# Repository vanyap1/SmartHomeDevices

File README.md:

# SmartHomeDevices
Smart Home consolidated devices project

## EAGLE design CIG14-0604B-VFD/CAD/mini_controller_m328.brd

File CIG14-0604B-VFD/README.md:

# CIG14-0604B-VFD
CIG14-0604B display controller 
Проект створено в Microchip studio.
Плата контролера - Eagle.

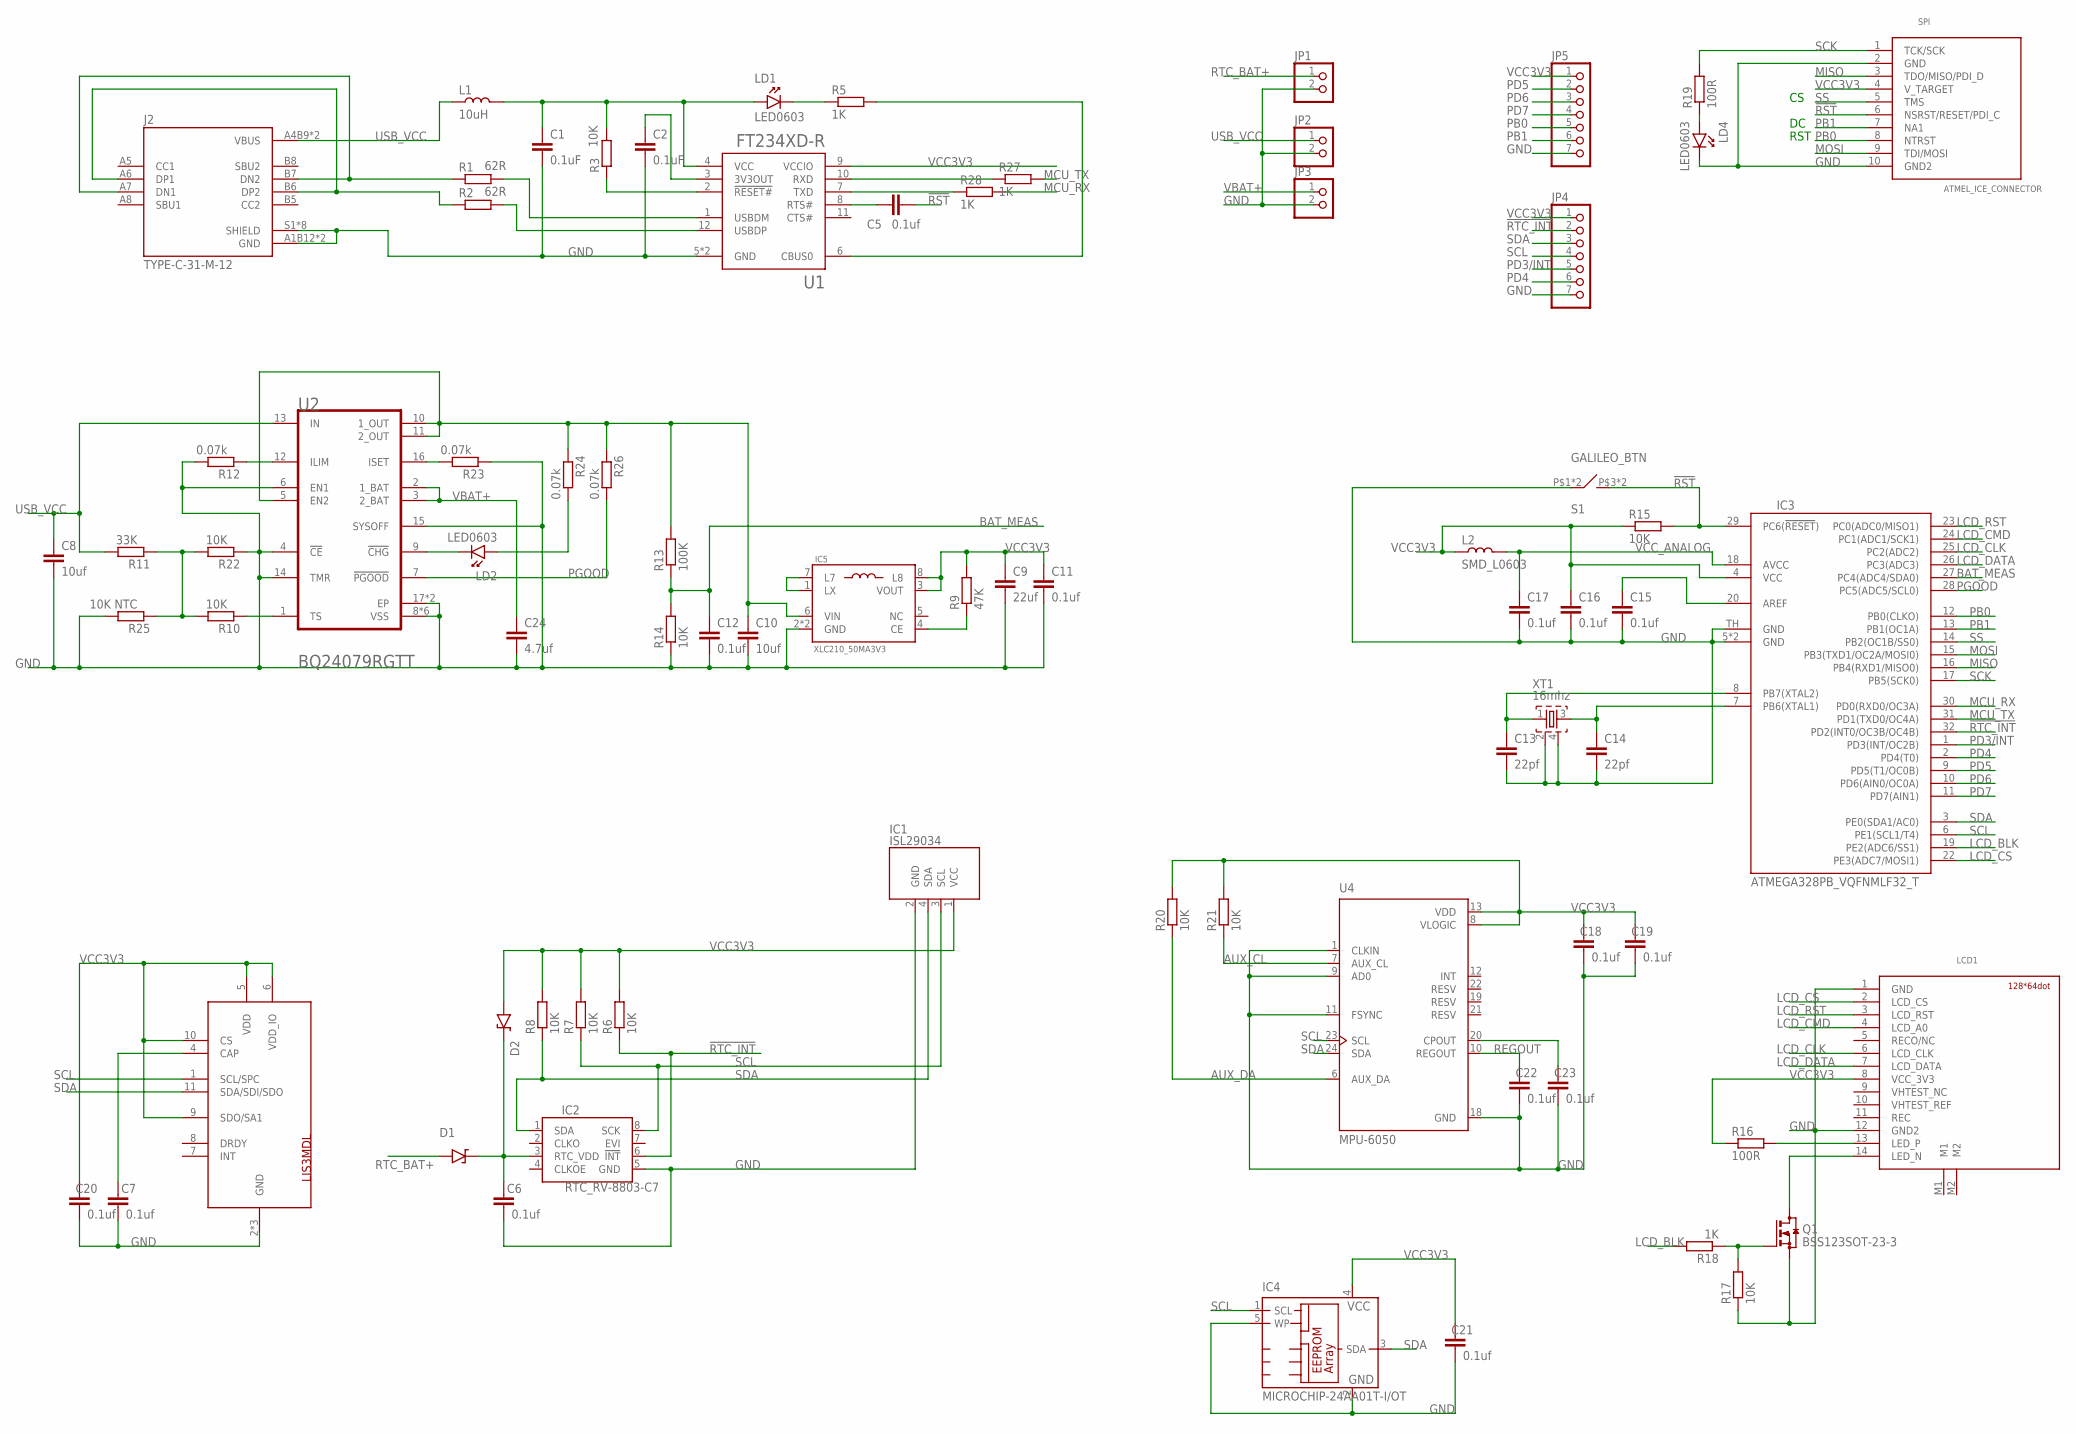
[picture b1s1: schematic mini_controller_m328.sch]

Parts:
C1, C2: 0.1uF; 0603
C5, C6, C7, C11, C12, C15, C16, C17, C18, C19, C20, C21, C22, C23: 0.1uf; 0603
C8: 10uf; 1206
C9: 22uf; 0805
C10: 10uf; 0603
C13, C14: 22pf; 0603
C24: 4.7uf; 0805
D1, D2: D_SOD323; SOD-323_D
IC1: ISL29034
IC2: RTC_RV-8803-C7; C7_RTC
IC3: ATMEGA328PB_VQFNMLF32_T; MLF32-TH
IC4: MICROCHIP-24AA01T-I/OT; SOT-23(5)
IC5: XLC210_50MA3V3; XCL210_50MA3V3
J2: TYPE-C-31-M-12; HRO_TYPE-C-31-M-12
JP1, JP2, JP3: PINHD-1X2; 1X02
JP4, JP5: PINHD-1X7; 1X07
L1: 10uH; 0603
L2: SMD_L0603; 0603
LCD1: ALE_LCD_128X64; ALE_LCD_14PIN_CONNECTOR
LD1, LD2, LD4: LED0603; 0603_P
Q1: BSS123SOT-23-3; SOT-23(3)
R1, R2: 62R; 0603
R3, R6, R7, R8, R10, R14, R15, R17, R20, R21, R22: 10K; 0603
R5, R18, R27, R28: 1K; 0603
R9: 47K; 0603
R11: 33K; 0603
R12, R23, R24, R26: 0.07k; 0603
R13: 100K; 0603
R16, R19: 100R; 0603
R25: 10K NTC; 0603
S1: GALILEO_BTN; GALILEO_VERT_BTN
SPI: ATMEL_ICE_CONNECTOR; MINI10P_SPI/JTAG/PDI
U1: FT234XD-R; IC_FT234XD-R
U2: TEXAS_INSTRUMENTS_BQ24079RGTTTEXAS_INSTRUMENTS_BQ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; TEXAS_INSTRUMENTS_BQ24079RGTT_0
U4: MPU-6050; QFN50P400X400X95-24N
U$1: LIS3MDL; LGA-12
XT1: 16mhz; QUARTZ_3X3MM

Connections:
!RST: C5.2, IC3.29 (PC6(!RESET!)), R15.2, S1.P$3 (4), S1.P$4 (4), SPI.6 (NSRST/RESET/PDI_C)
!RTC_INT: IC2.6 (!INT), IC3.32 (PD2(INT0/OC3B/OC4B)), JP4.2, R6.1
AUX_CL: R21.1, U4.7 (AUX_CL)
AUX_DA: R20.1, U4.6 (AUX_DA)
BAT_MEAS: C12.1, IC3.27 (PC4(ADC4/SDA0)), R13.1, R14.2
DM2: R1.2, U1.1 (USBDM)
DP2: R2.2, U1.12 (USBDP)
GND: C1.2, C2.2, C6.2, C7.2, C8.2, C9.2, C10.2, C11.2, C12.2, C13.2, C14.2, C15.2, C16.2, C17.2, C18.2, C19.2, C20.2, C21.2, C22.2, C23.2, C24.2, IC1.2 (GND), IC2.5 (GND), IC3.5 (GND), IC3.21 (GND), IC3.TH (GND), IC4.2 (GND), IC4.5 (WP), IC5.2 (GND), IC5.9 (GND), J2.A1B12 (GND), J2.B1A12 (GND), J2.S1 (SHIELD), J2.S2 (SHIELD), J2.S3 (SHIELD), J2.S4 (SHIELD), J2.S5 (SHIELD), J2.S6 (SHIELD), J2.S7 (SHIELD), J2.S8 (SHIELD), JP1.2, JP2.2, JP3.2, JP4.7, JP5.7, LCD1.1 (GND), LCD1.12 (GND2), LD4.1 (K), Q1.2 (S), R12.2, R14.1, R17.1, R22.1, R23.1, R25.2, S1.P$1 (1), S1.P$2 (1), SPI.2 (GND), SPI.10 (GND2), U1.5 (GND), U1.13 (GND), U2.4 (!CE!), U2.6 (EN1), U2.8 (VSS), U2.14 (TMR), U2.15 (SYSOFF), U2.17 (EP), U2.17-2 (EP), U2.PAD_1 (VSS), U2.PAD_2 (VSS), U2.PAD_3 (VSS), U2.PAD_4 (VSS), U2.PAD_5 (VSS), U4.1 (CLKIN), U4.9 (AD0), U4.11 (FSYNC), U4.18 (GND), U$1.2 (GND), U$1.3 (GND), U$1.12 (GND), XT1.2, XT1.4
LCD_BLK: IC3.19 (PE2(ADC6/SS1)), R18.2
LCD_CLK: IC3.25 (PC2(ADC2)), LCD1.6 (LCD_CLK)
LCD_CMD: IC3.24 (PC1(ADC1/SCK1)), LCD1.4 (LCD_A0)
LCD_CS: IC3.22 (PE3(ADC7/MOSI1)), LCD1.2 (LCD_CS)
LCD_DATA: IC3.26 (PC3(ADC3)), LCD1.7 (LCD_DATA)
LCD_RST: IC3.23 (PC0(ADC0/MISO1)), LCD1.3 (LCD_RST)
MCU_RX: IC3.30 (PD0(RXD0/OC3A)), R28.2
MCU_TX: IC3.31 (PD1(TXD0/OC4A)), R27.2
MISO: IC3.16 (PB4(RXD1/MISO0)), SPI.3 (TDO/MISO/PDI_D)
MOSI: IC3.15 (PB3(TXD1/OC2A/MOSI0)), SPI.9 (TDI/MOSI)
unnamed: LCD1.13 (LED_P), R16.2
unnamed: LCD1.14 (LED_N), Q1.3 (D)
unnamed: IC5.1 (LX), IC5.7 (L7)
unnamed: Q1.1 (G), R17.2, R18.1
unnamed: IC5.4 (CE), R9.1
unnamed: R10.2, R11.1, R22.2, R25.1
unnamed: C1.1, L1.2, LD1.2 (A), R3.2, U1.4 (VCC)
unnamed: C13.1, IC3.8 (PB7(XTAL2)), XT1.1
unnamed: C2.1, U1.3 (3V3OUT)
unnamed: LD1.1 (K), R5.1
unnamed: R5.2, U1.6 (CBUS0)
unnamed: C14.1, IC3.7 (PB6(XTAL1)), XT1.3
unnamed: LD2.1 (K), U2.9 (!CHG!)
unnamed: R27.1, U1.10 (RXD)
unnamed: C5.1, U1.8 (RTS#)
unnamed: LD4.2 (A), R19.1
unnamed: C23.1, U4.20 (CPOUT)
unnamed: R10.1, U2.1 (TS)
unnamed: C6.1, D1.K, D2.K, IC2.3 (RTC_VDD)
unnamed: C15.1, IC3.20 (AREF)
unnamed: J2.A7 (DN1), J2.B7 (DN2), R1.1
unnamed: J2.A6 (DP1), J2.B6 (DP2), R2.1
unnamed: R12.1, U2.12 (ILIM)
unnamed: C10.1, IC5.6 (VIN), R13.2, R24.1, R26.1, U2.5 (EN2), U2.10 (1_OUT), U2.11 (2_OUT)
unnamed: LD2.2 (A), R24.2
unnamed: R23.2, U2.16 (ISET)
unnamed: R28.1, U1.7 (TXD)
unnamed: C7.1, U$1.4 (CAP)
PB0: IC3.12 (PB0(CLKO)), JP5.5, SPI.8 (NTRST)
PB1: IC3.13 (PB1(OC1A)), JP5.6, SPI.7 (NA1)
PD3/INT: IC3.1 (PD3(INT/OC2B)), JP4.5
PD4: IC3.2 (PD4(T0)), JP4.6
PD5: IC3.9 (PD5(T1/OC0B)), JP5.2
PD6: IC3.10 (PD6(AIN0/OC0A)), JP5.3
PD7: IC3.11 (PD7(AIN1)), JP5.4
PGOOD: IC3.28 (PC5(ADC5/SCL0)), R26.2, U2.7 (!PGOOD!)
REGOUT: C22.1, U4.10 (REGOUT)
RTC_BAT+: D1.A, JP1.1
SCK: IC3.17 (PB5(SCK0)), R19.2, SPI.1 (TCK/SCK)
SCL: IC1.3 (SCL), IC2.8 (SCK), IC3.6 (PE1(SCL1/T4)), IC4.1 (SCL), JP4.4, R7.1, U4.23 (SCL), U$1.1 (SCL/SPC)
SDA: IC1.4 (SDA), IC2.1 (SDA), IC3.3 (PE0(SDA1/AC0)), IC4.3 (SDA), JP4.3, R8.1, U4.24 (SDA), U$1.11 (SDA/SDI/SDO)
SER_RST: R3.1, U1.2 (!RESET#)
SS: IC3.14 (PB2(OC1B/SS0)), SPI.5 (TMS)
USB_VCC: C8.1, J2.A4B9 (VBUS), J2.B4A9 (VBUS), JP2.1, L1.1, R11.2, U2.13 (IN)
VBAT+: C24.1, JP3.1, U2.2 (1_BAT), U2.3 (2_BAT)
VCC3V3: C9.1, C11.1, C16.1, C18.1, C19.1, C20.1, C21.1, D2.A, IC1.1 (VCC), IC3.4 (VCC), IC4.4 (VCC), IC5.3 (VOUT), IC5.8 (L8), JP4.1, JP5.1, L2.1, LCD1.8 (VCC_3V3), R6.2, R7.2, R8.2, R9.2, R15.1, R16.1, R20.2, R21.2, SPI.4 (V_TARGET), U1.9 (VCCIO), U4.8 (VLOGIC), U4.13 (VDD), U$1.5 (VDD), U$1.6 (VDD_IO), U$1.9 (SDO/SA1), U$1.10 (CS)
VCC_ANALOG: C17.1, IC3.18 (AVCC), L2.2

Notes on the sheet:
RST

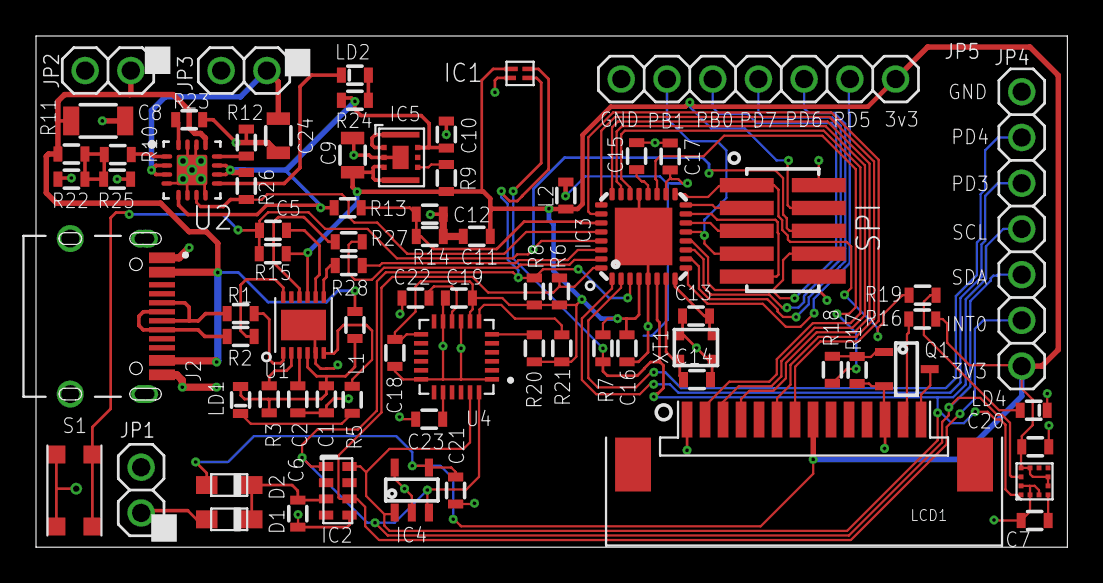
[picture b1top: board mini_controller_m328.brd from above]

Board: 2 copper layers, 57.3 x 28.4 mm, 76 parts (0 on the bottom side), 65 nets.

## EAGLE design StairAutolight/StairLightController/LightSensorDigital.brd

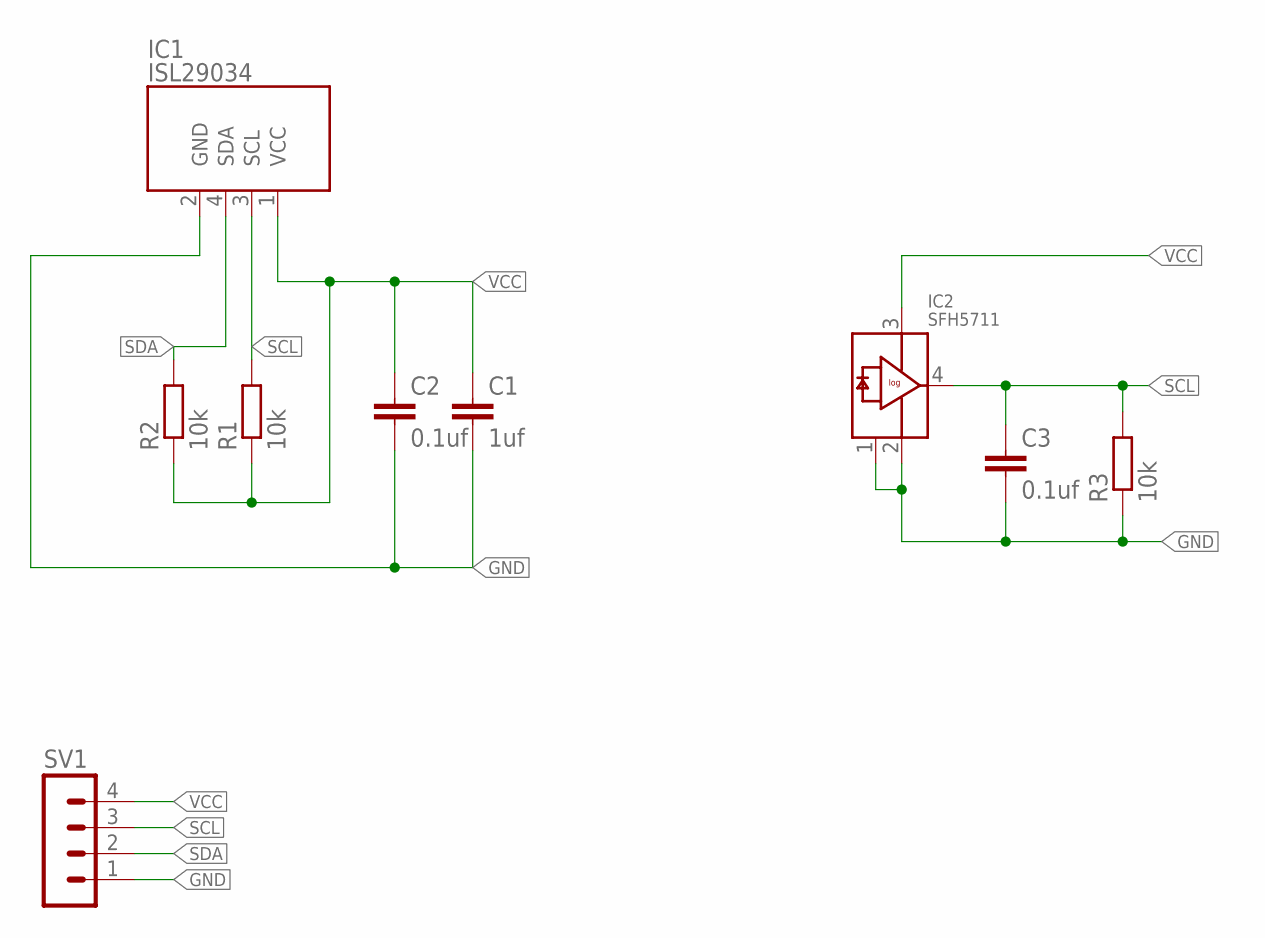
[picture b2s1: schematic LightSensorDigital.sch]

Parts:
C1: 1uf; 0603
C2, C3: 0.1uf; 0603
IC1: ISL29034
IC2: SFH5711
R1, R2, R3: 10k; 0603
SV1: MA04-1

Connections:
GND: C1.2, C2.2, C3.2, IC1.2 (GND), IC2.1, IC2.2, R3.1, SV1.1
SCL: C3.1, IC1.3 (SCL), IC2.4, R1.2, R3.2, SV1.3
SDA: IC1.4 (SDA), R2.2, SV1.2
VCC: C1.1, C2.1, IC1.1 (VCC), IC2.3, R1.1, R2.1, SV1.4

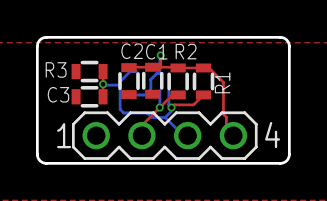
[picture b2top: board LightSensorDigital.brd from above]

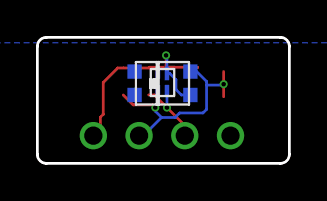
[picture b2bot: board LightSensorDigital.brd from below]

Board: 2 copper layers, 14.0 x 7.0 mm, 9 parts (2 on the bottom side), 4 nets.

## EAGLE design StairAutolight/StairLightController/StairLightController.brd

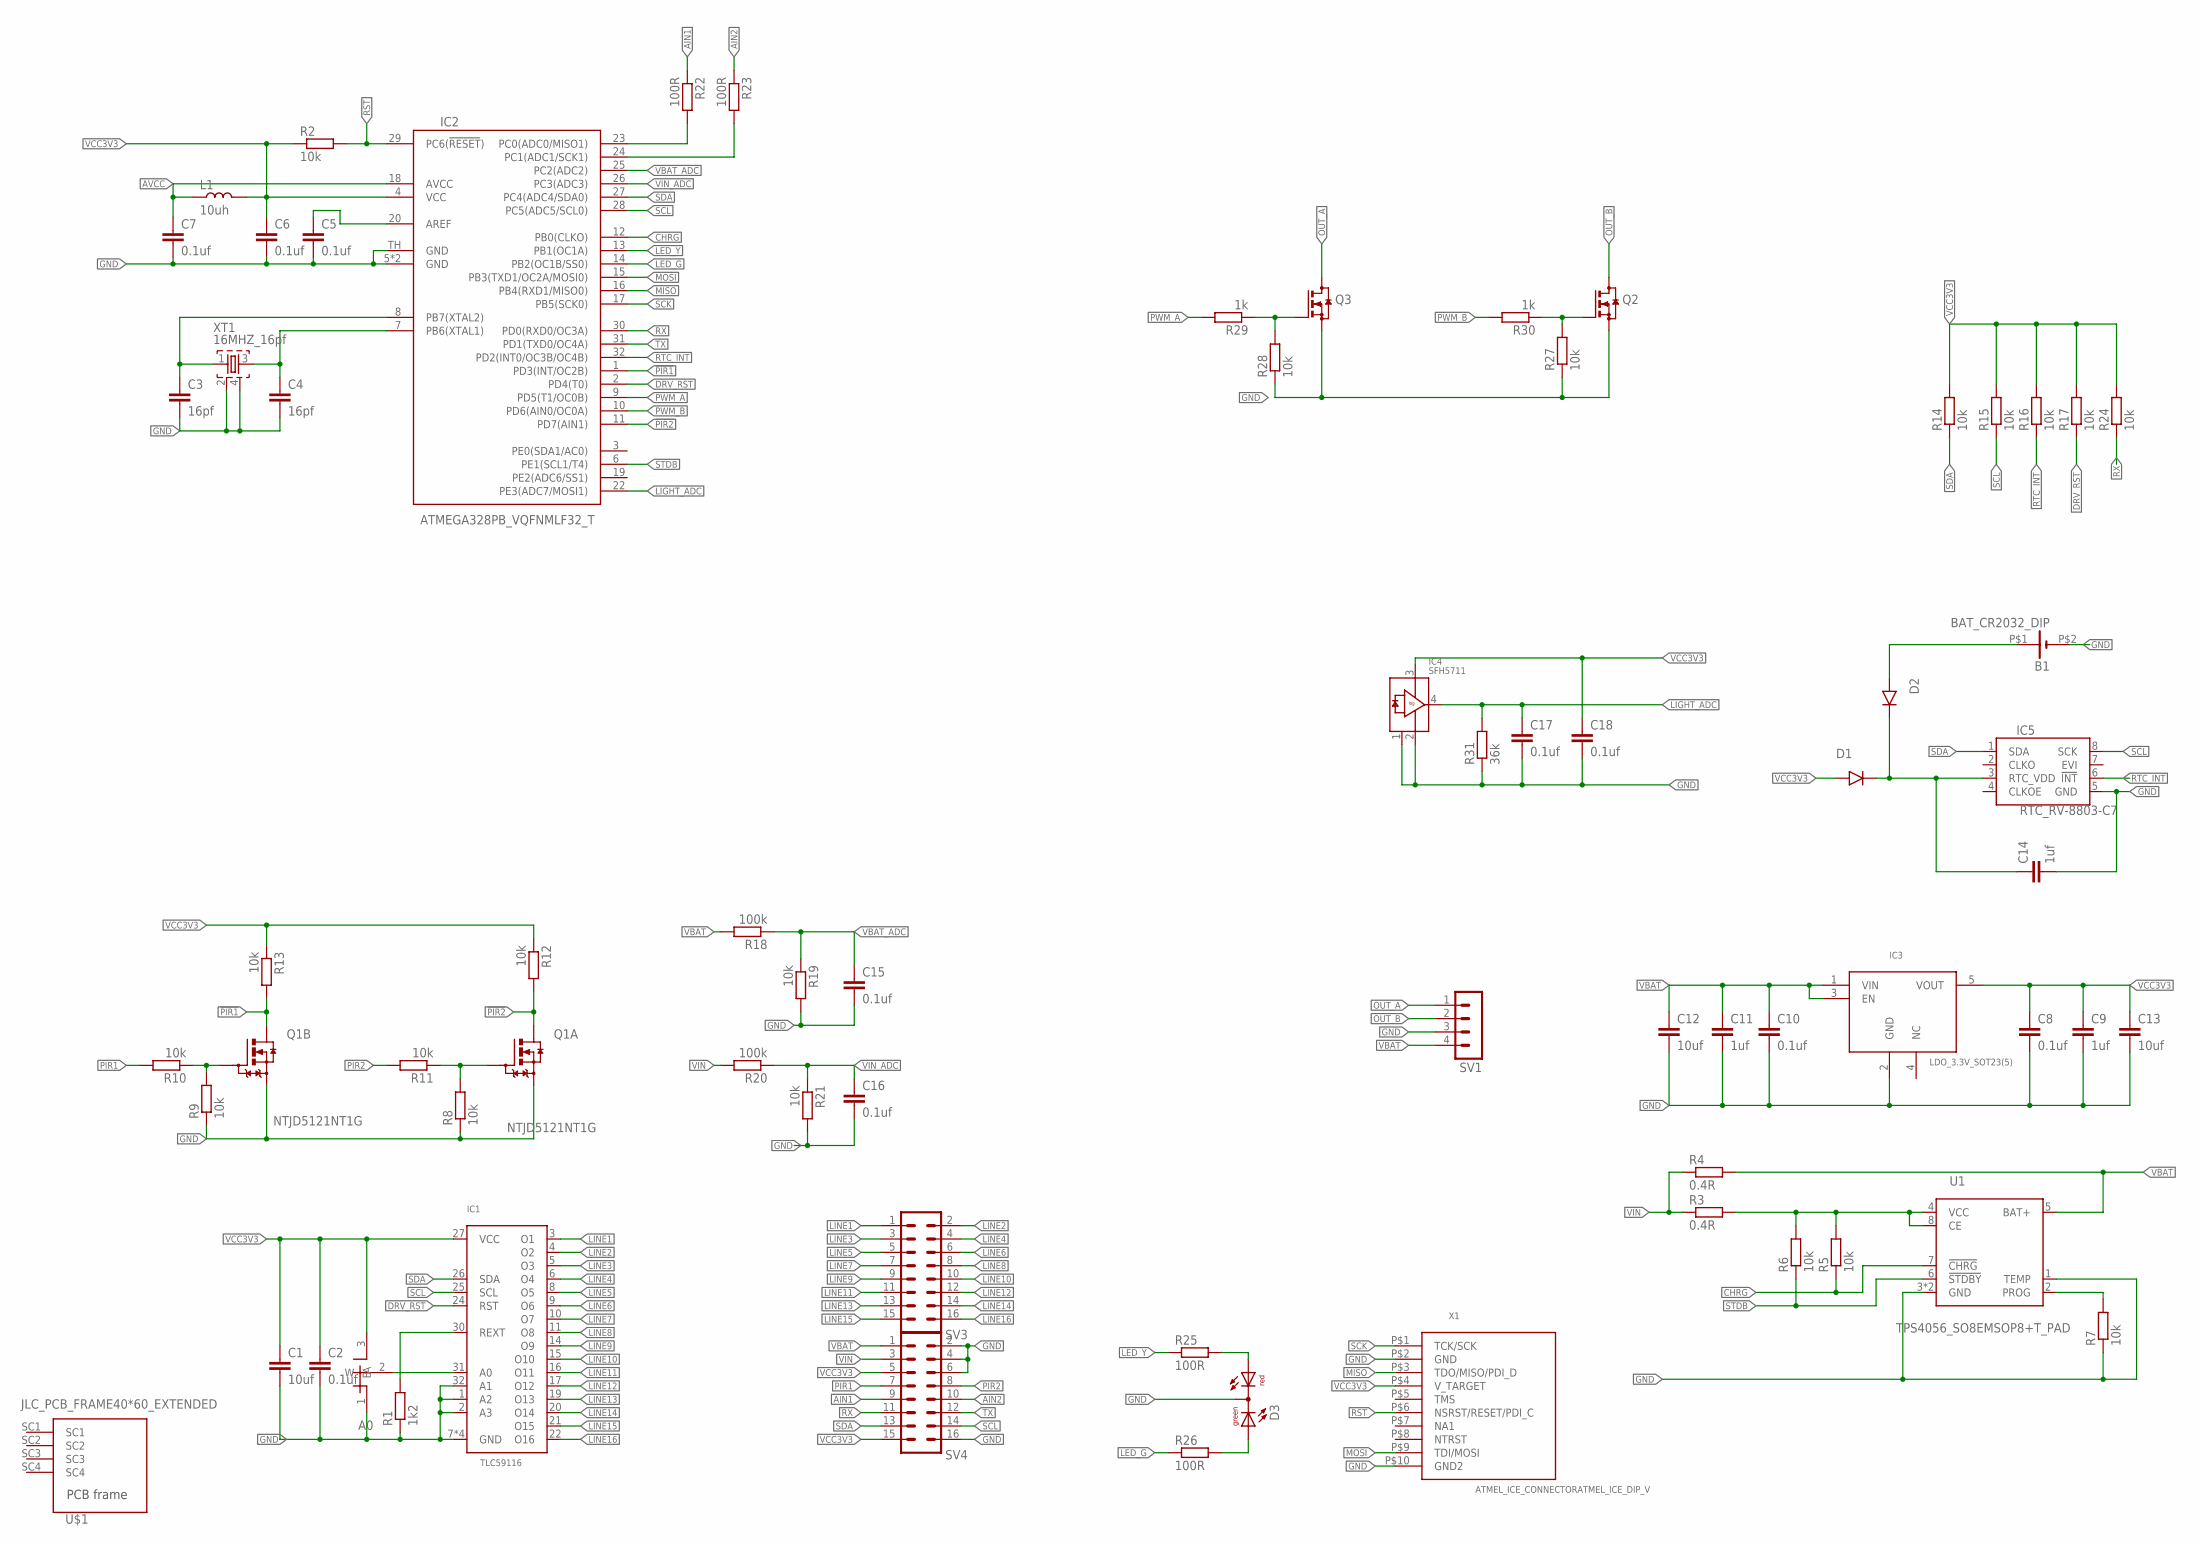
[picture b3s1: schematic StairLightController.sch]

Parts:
A0: SMD_SWITCH_JUMPER; 0603_JUMP
B1: BAT_CR2032_DIP; CR2032_DIP
C1: 10uf; 0603
C2, C5, C6, C7, C8, C10, C15, C16, C17, C18: 0.1uf; 0603
C3, C4: 16pf; 0603
C9, C11, C14: 1uf; 0603
C12, C13: 10uf; 1206
D1, D2: L1N4148WT1GSOD123_GALILE0_SMALL; SOD-123_MINI-SMA
D3: DUOLED5MM
IC1: TLC59116; MLF32-TH
IC2: ATMEGA328PB_VQFNMLF32_T; MLF32-TH
IC3: LDO_3.3V_SOT23(5); SOT-23(5)
IC4: SFH5711
IC5: RTC_RV-8803-C7; C7_RTC
L1: 10uh; 0603
Q1: NTJD5121NT1G; SOT363
Q2, Q3: BSS123SOT-23-3; SOT-23(3)
R1: 1k2; 0603
R2, R5, R6, R7, R8, R9, R10, R11, R12, R13, R14, R15, R16, R17, R19, R21, R24, R27, R28: 10k; 0603
R3, R4: 0.4R; 1206
R18, R20: 100k; 0603
R22, R23, R25, R26: 100R; 0603
R29, R30: 1k; 0603
R31: 36k; 0603
SV1: MA04-1
SV3, SV4: MA08-2
U1: TPS4056_SO8EMSOP8+T_PAD; EMSOP8+TPAD
U$1: JLC_PCB_FRAME40*60_EXTENDED; 40X60_SENSOR_UNIT_OPEN
X1: ATMEL_ICE_CONNECTORATMEL_ICE_DIP_V; MINI10P_SPI/JTAG/PDI_DIP_V
XT1: 16MHZ_16pf; QUARTZ_3X3MM

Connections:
!PIR1: IC2.1 (PD3(INT/OC2B)), Q1.3 (D), R13.2
!PIR2: IC2.11 (PD7(AIN1)), Q1.6 (D), R12.2
AIN1: R22.1, SV4.9
AIN2: R23.1, SV4.10
AVCC: C7.1, IC2.18 (AVCC), L1.1
CHRG: IC2.12 (PB0(CLKO)), R5.1, U1.7 (!CHRG)
DRV_RST: IC1.24 (RST), IC2.2 (PD4(T0)), R17.1
GND: A0.1 (A), B1.P$2 (-), C1.2, C2.2, C3.2, C4.2, C5.2, C6.2, C7.2, C8.2, C9.2, C10.2, C11.2, C12.2, C13.2, C14.2, C15.2, C16.2, C17.2, C18.2, D3.K (C), IC1.1 (A2), IC1.2 (A3), IC1.7 (GND), IC1.18 (GND), IC1.23 (GND), IC1.32 (A1), IC1.TH (GND), IC2.5 (GND), IC2.21 (GND), IC2.TH (GND), IC3.2 (GND), IC4.1, IC4.2, IC5.5 (GND), Q1.1 (S), Q1.4 (S), Q2.2 (S), Q3.2 (S), R1.1, R7.1, R8.1, R9.1, R19.2, R21.2, R27.1, R28.1, R31.1, SV1.3, SV4.2, SV4.4, SV4.6, SV4.16, U1.1 (TEMP), U1.3 (GND), U1.TPAD (GND), X1.P$2 (GND), X1.P$10 (GND2), XT1.2, XT1.4
LED_G: IC2.14 (PB2(OC1B/SS0)), R26.1
LED_Y: IC2.13 (PB1(OC1A)), R25.1
LIGHT_ADC: C17.1, IC2.22 (PE3(ADC7/MOSI1)), IC4.4, R31.2
LINE1: IC1.3 (O1), SV3.1
LINE2: IC1.4 (O2), SV3.2
LINE3: IC1.5 (O3), SV3.3
LINE4: IC1.6 (O4), SV3.4
LINE5: IC1.8 (O5), SV3.5
LINE6: IC1.9 (O6), SV3.6
LINE7: IC1.10 (O7), SV3.7
LINE8: IC1.11 (O8), SV3.8
LINE9: IC1.14 (O9), SV3.9
LINE10: IC1.15 (O10), SV3.10
LINE11: IC1.16 (O11), SV3.11
LINE12: IC1.17 (O12), SV3.12
LINE13: IC1.19 (O13), SV3.13
LINE14: IC1.20 (O14), SV3.14
LINE15: IC1.21 (O15), SV3.15
LINE16: IC1.22 (O16), SV3.16
MISO: IC2.16 (PB4(RXD1/MISO0)), X1.P$3 (TDO/MISO/PDI_D)
MOSI: IC2.15 (PB3(TXD1/OC2A/MOSI0)), X1.P$9 (TDI/MOSI)
unnamed: A0.2 (W), IC1.31 (A0)
unnamed: IC1.30 (REXT), R1.2
unnamed: C3.1, IC2.8 (PB7(XTAL2)), XT1.1
unnamed: C4.1, IC2.7 (PB6(XTAL1)), XT1.3
unnamed: R7.2, U1.2 (PROG)
unnamed: R3.2, R5.2, R6.2, U1.4 (VCC), U1.8 (CE)
unnamed: C5.1, IC2.20 (AREF)
unnamed: IC2.23 (PC0(ADC0/MISO1)), R22.2
unnamed: Q1.2 (G), R8.2, R11.1
unnamed: D3.AR, R25.2
unnamed: Q1.5 (G), R9.2, R10.1
unnamed: IC2.24 (PC1(ADC1/SCK1)), R23.2
unnamed: C14.1, D1.C, D2.C, IC5.3 (RTC_VDD)
unnamed: D3.AG, R26.2
unnamed: Q2.1 (G), R27.2, R30.1
unnamed: B1.P$1 (+), D2.A
unnamed: Q3.1 (G), R28.2, R29.1
OUT_A: Q3.3 (D), SV1.1
OUT_B: Q2.3 (D), SV1.2
PIR1: R10.2, SV4.7
PIR2: R11.2, SV4.8
PWM_A: IC2.9 (PD5(T1/OC0B)), R29.2
PWM_B: IC2.10 (PD6(AIN0/OC0A)), R30.2
RST: IC2.29 (PC6(!RESET!)), R2.2, X1.P$6 (NSRST/RESET/PDI_C)
RTC_INT: IC2.32 (PD2(INT0/OC3B/OC4B)), IC5.6 (!INT), R16.1
RX: IC2.30 (PD0(RXD0/OC3A)), R24.1, SV4.11
SCK: IC2.17 (PB5(SCK0)), X1.P$1 (TCK/SCK)
SCL: IC1.25 (SCL), IC2.28 (PC5(ADC5/SCL0)), IC5.8 (SCK), R15.1, SV4.14
SDA: IC1.26 (SDA), IC2.27 (PC4(ADC4/SDA0)), IC5.1 (SDA), R14.1, SV4.13
STDB: IC2.6 (PE1(SCL1/T4)), R6.1, U1.6 (!STDBY)
TX: IC2.31 (PD1(TXD0/OC4A)), SV4.12
VBAT: C10.1, C11.1, C12.1, IC3.1 (VIN), IC3.3 (EN), R4.2, R18.2, SV1.4, SV4.1, U1.5 (BAT+)
VBAT_ADC: C15.1, IC2.25 (PC2(ADC2)), R18.1, R19.1
VCC3V3: A0.3 (B), C1.1, C2.1, C6.1, C8.1, C9.1, C13.1, C18.1, D1.A, IC1.27 (VCC), IC2.4 (VCC), IC3.5 (VOUT), IC4.3, L1.2, R2.1, R12.1, R13.1, R14.2, R15.2, R16.2, R17.2, R24.2, SV4.5, SV4.15, X1.P$4 (V_TARGET)
VIN: R3.1, R4.1, R20.2, SV4.3
VIN_ADC: C16.1, IC2.26 (PC3(ADC3)), R20.1, R21.1

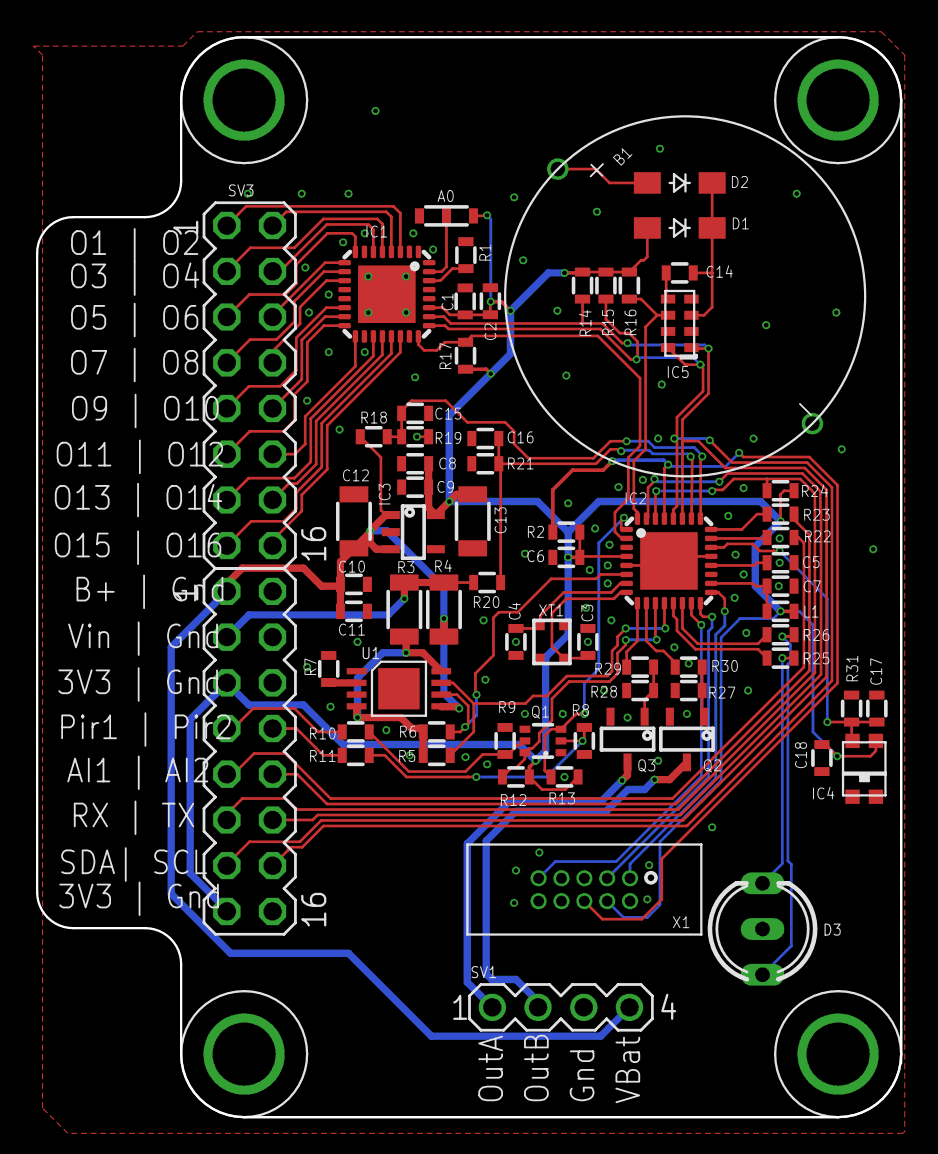
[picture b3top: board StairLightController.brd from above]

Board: 2 copper layers, 48.0 x 60.0 mm, 70 parts (0 on the bottom side), 65 nets.

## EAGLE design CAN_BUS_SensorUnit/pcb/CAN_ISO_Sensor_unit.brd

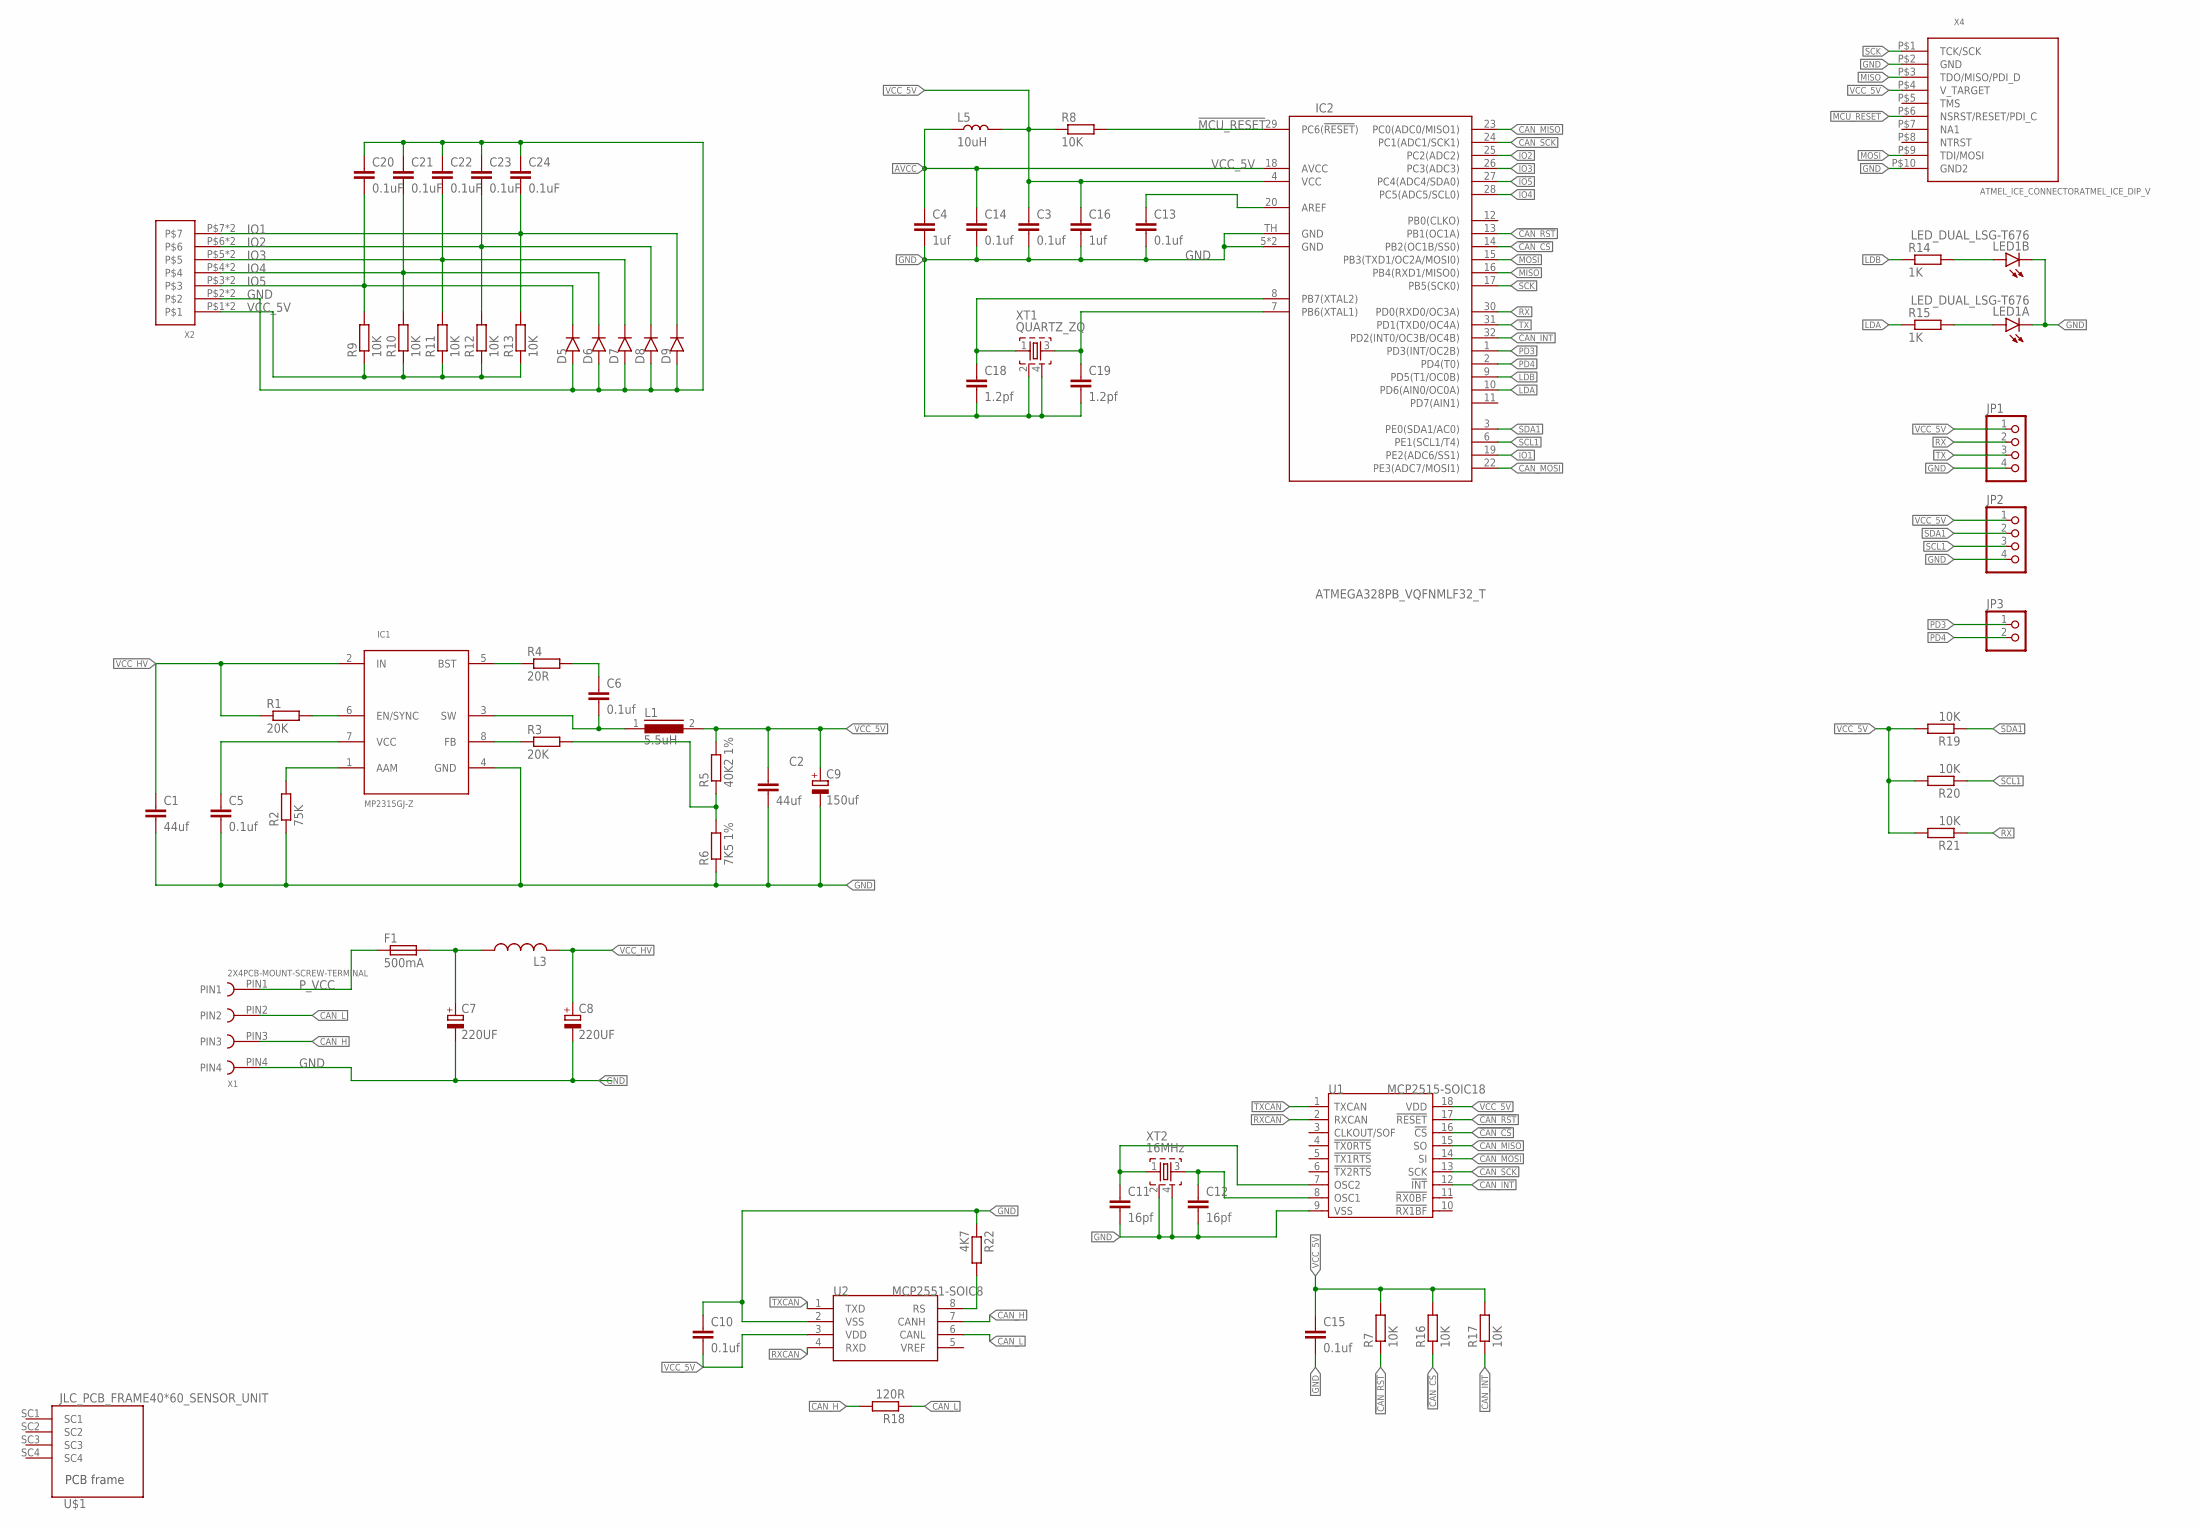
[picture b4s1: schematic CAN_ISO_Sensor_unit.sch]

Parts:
C1, C2: 44uf; 3528_NP
C3, C5, C6, C10, C13, C14, C15: 0.1uf; 0603
C4, C16: 1uf; 0603
C7, C8: 220UF; 3.6MM
C9: 150uf; D/7343-31R
C11, C12: 16pf; 0603
C18, C19: 1.2pf; 0603
C20, C21, C22, C23, C24: 0.1uF; 0603
D5, D6, D7, D8, D9: L1N4148WT1GSOD123_GALILE0_SMALL; SOD-123_MINI-SMA
F1: 500mA; SMD_2410_FUSE_NOK
IC1: MP2315GJ-Z; TSOT23-8
IC2: ATMEGA328PB_VQFNMLF32_T; MLF32-TH
JP1, JP2: PINHD-1X4; 1X04
JP3: PINHD-1X2; 1X02
L1: 5.5uH; DR73
L3: L-US0207/2V; 0207/2V
L5: 10uH; 0805
LED1: LED_DUAL_LSG-T676; P-LCC4-0
R1, R3: 20K; 0603
R2: 75K; 0603
R4: 20R; 0603
R5: 40K2 1%; 0603
R6: 7K5 1%; 0603
R7, R8, R9, R10, R11, R12, R13, R16, R17, R19, R20, R21: 10K; 0603
R14, R15: 1K; 0603
R18: 120R; 0603
R22: 4K7; 0603
U1: MCP2515-SOIC18; SO18L
U2: MCP2551-SOIC8; SO8
U$1: JLC_PCB_FRAME40*60_SENSOR_UNIT; 40X60_SENSOR_UNIT
X1: 2X4PCB-MOUNT-SCREW-TERMINAL
X2: WAGO250_X7; WAGO250_FP_7X
X4: ATMEL_ICE_CONNECTORATMEL_ICE_DIP_V; MINI10P_SPI/JTAG/PDI_DIP_V
XT1: QUARTZ_ZQ; QUARTZ_3X3MM
XT2: 16MHz; QUARTZ_3X3MM

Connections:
!CAN_CS: IC2.14 (PB2(OC1B/SS0)), R16.1, U1.16 (!CS)
!CAN_RST: IC2.13 (PB1(OC1A)), R7.1, U1.17 (!RESET)
!MCU_RESET: IC2.29 (PC6(!RESET!)), R8.2, X4.P$6 (NSRST/RESET/PDI_C)
AREF: C13.1, IC2.20 (AREF)
AVCC: C4.1, C14.1, IC2.18 (AVCC), L5.1
CAN_H: R18.2, U2.7 (CANH), X1.PIN3
CAN_INT: IC2.32 (PD2(INT0/OC3B/OC4B)), R17.1, U1.12 (!INT)
CAN_L: R18.1, U2.6 (CANL), X1.PIN2
CAN_MISO: IC2.23 (PC0(ADC0/MISO1)), U1.15 (SO)
CAN_MOSI: IC2.22 (PE3(ADC7/MOSI1)), U1.14 (SI)
CAN_SCK: IC2.24 (PC1(ADC1/SCK1)), U1.13 (SCK)
FB: R3.2, R5.1, R6.2
GND: C1.P (2), C2.P (2), C3.2, C4.2, C5.2, C7.P$1 (-), C8.P$1 (-), C9.-, C10.1, C11.2, C12.2, C13.2, C14.2, C15.2, C16.2, C18.2, C19.2, C20.1, C21.1, C22.1, C23.1, C24.1, D5.A, D6.A, D7.A, D8.A, D9.A, IC1.4 (GND), IC2.5 (GND), IC2.21 (GND), IC2.TH (GND), JP1.4, JP2.4, LED1.1 (C), LED1.3 (C), R2.1, R6.1, R22.1, U1.9 (VSS), U2.2 (VSS), X1.PIN4, X2.P$2, X2.U$2, X4.P$2 (GND), X4.P$10 (GND2), XT1.2, XT1.4, XT2.2, XT2.4
IO1: C24.2, D9.C, IC2.19 (PE2(ADC6/SS1)), R13.2, X2.P$7, X2.U$7
IO2: C23.2, D8.C, IC2.25 (PC2(ADC2)), R12.2, X2.P$6, X2.U$6
IO3: C22.2, D7.C, IC2.26 (PC3(ADC3)), R11.2, X2.P$5, X2.U$5
IO4: C21.2, D6.C, IC2.28 (PC5(ADC5/SCL0)), R10.2, X2.P$4, X2.U$4
IO5: C20.2, D5.C, IC2.27 (PC4(ADC4/SDA0)), R9.2, X2.P$3, X2.U$3
LDA: IC2.10 (PD6(AIN0/OC0A)), R15.1
LDB: IC2.9 (PD5(T1/OC0B)), R14.1
MISO: IC2.16 (PB4(RXD1/MISO0)), X4.P$3 (TDO/MISO/PDI_D)
MOSI: IC2.15 (PB3(TXD1/OC2A/MOSI0)), X4.P$9 (TDI/MOSI)
unnamed: C7.P$2 (+), F1.P$2 (2), L3.1
unnamed: IC1.1 (AAM), R2.2
unnamed: LED1.4 (A), R14.2
unnamed: LED1.2 (A), R15.2
unnamed: C5.1, IC1.7 (VCC)
unnamed: IC1.6 (EN/SYNC), R1.2
unnamed: C12.1, U1.8 (OSC1), XT2.3
unnamed: C11.1, U1.7 (OSC2), XT2.1
unnamed: IC1.5 (BST), R4.1
unnamed: C6.1, R4.2
unnamed: C6.2, IC1.3 (SW), L1.1
unnamed: IC1.8 (FB), R3.1
unnamed: R22.2, U2.8 (RS)
unnamed: C18.1, IC2.8 (PB7(XTAL2)), XT1.1
unnamed: C19.1, IC2.7 (PB6(XTAL1)), XT1.3
PD3: IC2.1 (PD3(INT/OC2B)), JP3.1
PD4: IC2.2 (PD4(T0)), JP3.2
P_VCC: F1.P$1 (1), X1.PIN1
RX: IC2.30 (PD0(RXD0/OC3A)), JP1.2, R21.1
RXCAN: U1.2 (RXCAN), U2.4 (RXD)
SCK: IC2.17 (PB5(SCK0)), X4.P$1 (TCK/SCK)
SCL1: IC2.6 (PE1(SCL1/T4)), JP2.3, R20.1
SDA1: IC2.3 (PE0(SDA1/AC0)), JP2.2, R19.1
TX: IC2.31 (PD1(TXD0/OC4A)), JP1.3
TXCAN: U1.1 (TXCAN), U2.1 (TXD)
VCC_5V: C2.M (1), C3.1, C9.+, C10.2, C15.1, C16.1, IC2.4 (VCC), JP1.1, JP2.1, L1.2, L5.2, R5.2, R7.2, R8.1, R9.1, R10.1, R11.1, R12.1, R13.1, R16.2, R17.2, R19.2, R20.2, R21.2, U1.18 (VDD), U2.3 (VDD), X2.P$1, X2.U$1, X4.P$4 (V_TARGET)
VCC_HV: C1.M (1), C8.P$2 (+), IC1.2 (IN), L3.2, R1.1

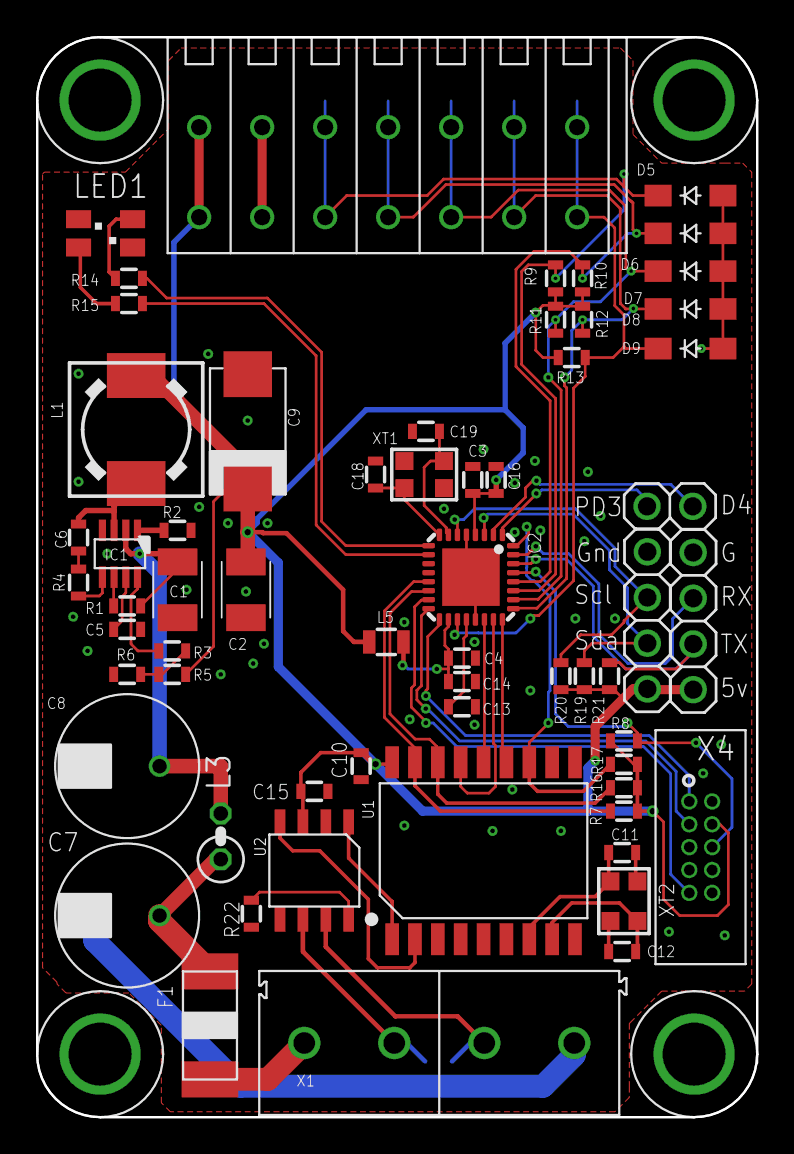
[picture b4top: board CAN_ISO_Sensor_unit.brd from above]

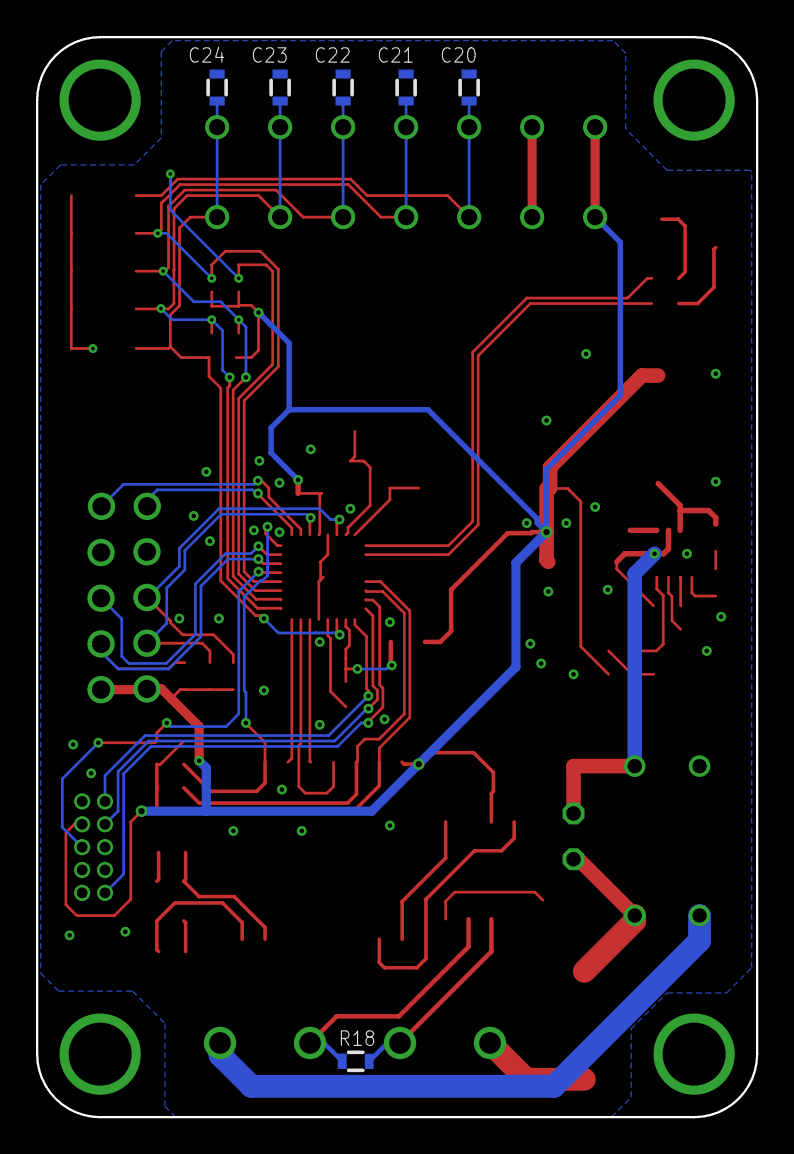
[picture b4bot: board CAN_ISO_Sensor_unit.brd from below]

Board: 2 copper layers, 40.0 x 60.0 mm, 68 parts (6 on the bottom side), 49 nets.
